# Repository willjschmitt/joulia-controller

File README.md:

# joulia-controller

Controller for the electric brewing hardware.

## Quickstart
Install Raspbian on a fresh SD card, and boot your Raspberry Pi.

Enable SSH (optional), for installing remotely. Make sure the password for the
main account is changed to a secure password. Enable I2C and SPI.

Install Anaconda (Miniconda), using the default options (installing to
`/home/pi/miniconda`):
```
wget http://repo.continuum.io/miniconda/Miniconda3-latest-Linux-armv7l.sh
bash Miniconda3-latest-Linux-arm71.sh
```
Answer all questions posed.

Clone the source:
```git clone https://github.com/willjschmitt/joulia-controller.git```

Create a conda environment and install the dependencies:
```
cd joulia-controller
/home/pi/miniconda3/bin/conda create --name joulia-controller python=3
source /home/pi/miniconda3/bin/activate joulia-controller
pip install -r requirements.txt
```

Create a log directory for joulia and change the owner to pi:
```
sudo mkdir /var/log/joulia
sudo chown pi:pi /var/log/joulia
```

### Automatic Startup
To automatically, launch the software on startup, install the contents from
`crontab` into the root cron table using:
```
sudo crontab -e
```

In the crontab, you must update the environment variables in angle brackets per
the definitions:
 * `JOULIA_WEBSERVER_HOST` - The webserver this controller should stream data to
   (usually `joulia.io`)
 * `JOULIA_WEBSERVER_AUTHTOKEN` - The authtoken provided in your dashboard on
   joulia.io, used to authenticate the controller and identify controller
   information.

### Manual Startup
Run the controller:
```
cd joulia-controller
source /home/pi/miniconda3/bin/activate joulia-controller
export JOULIA_WEBSERVER_HOST=joulia.io
export JOULIA_WEBSERVER_AUTHTOKEN=<insert token>
python main.py
```

## Connections to Hardware
This project is meant to be run on a Raspberry Pi and makes use of the GPIO pins.

### Analog Measurement
Make sure I2C is appropriately turned on on the Raspberry Pi. Install the Arduino I2C Analog Reader software onto the Arduino, so it can communicate the temperature measurements to the Raspberry Pi.

### Digital Control
Connect the Solid State Relay input gate for the Boil Kettle to Pin 0 on the Raspberry Pi.
Connect the Solid State Relay input gate for the Main Pump to Pin 1 on the Raspberry Pi.

## Related Projects
This project is part of the series of projects for the Joulia Brewing System:
* [joulia-webserver](https://github.com/willjschmitt/joulia-webserver) - Remote webserver to log data and allow for livestreaming of data to other clients and receive commands from other clients.
* [joulia-controller](https://github.com/willjschmitt/joula-controller) - This project.
* joulia-fermentation - Planned project to control the fementation operations.

## Licensing
Copyright 2016 William Schmitt. All Rights Reserved.

The intention is to make this project open-sourced, but at this moment is maintained under personal copyright until a few things can be worked through.

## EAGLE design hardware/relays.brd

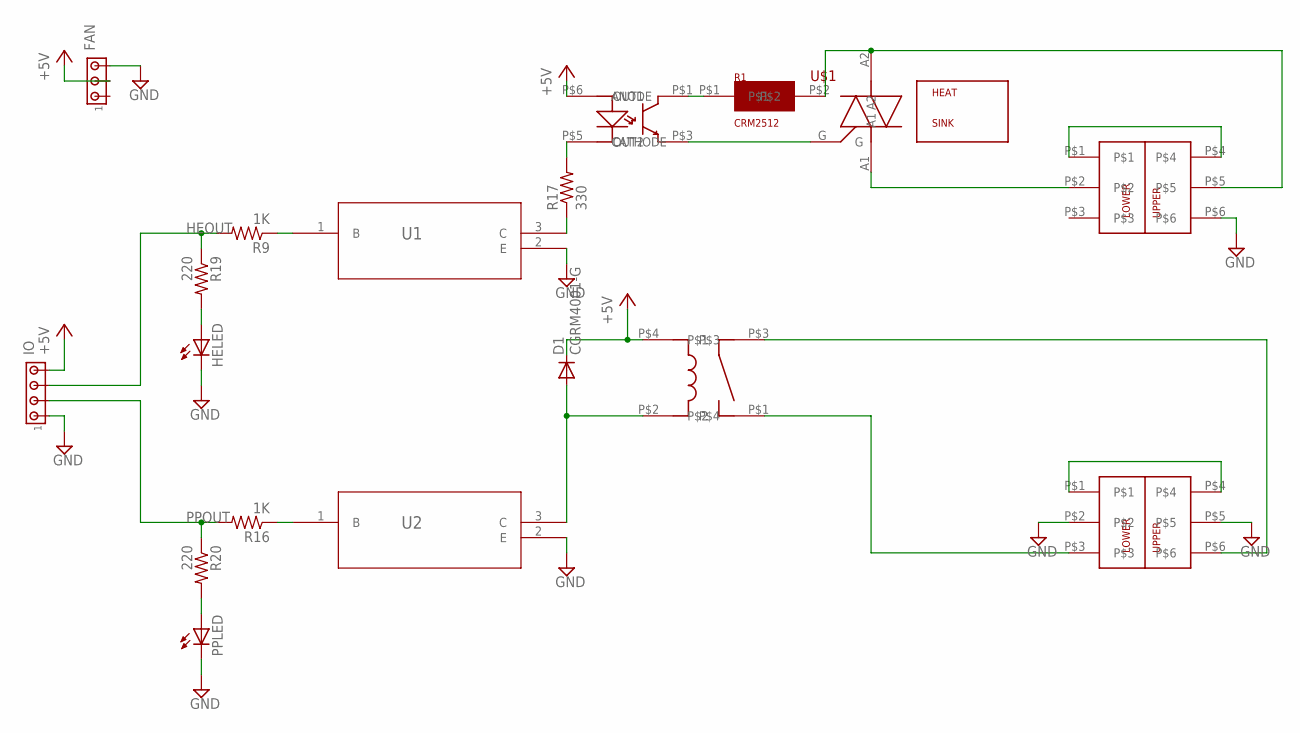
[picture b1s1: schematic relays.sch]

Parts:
D1: CGRM4001-G; SOD-123_MINI-SMA
FAN: MTA03-100; 10X03MTA
HELED: LED_ESML0603; LED_SML0603
IO: MTA04-100; 10X04MTA
PPLED: LED_ESML0603; LED_SML0603
R1: CRM2512; 2512(6432METRIC)
R9, R16: 1K; R0402
R17: 330; R1206
R19, R20: 220; R0402
U1, U2: MMBT2222ALT1G; SOT-23
U$1: T3050H-6I; TO-220
U$2: VM1-038-1AEHORIZONTAL; VM2-038-1AE
U$3: G5LE-1A4_DC5
U$4: PC1725041; PC-MKKDS1.5/3-5.08
U$5: MOC3020S; 6-SMD
U$6: PC1719028; PC-MKKDS5/3-9.5

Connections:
120H: U$3.P$1, U$4.P$3
120N: U$4.P$1, U$4.P$4
+5V: D1.C, FAN.2, IO.4, U$3.P$4, U$5.P$6 (ANODE)
+120: U$6.P$1, U$6.P$4
-120: U$1.A1, U$6.P$2
GND: FAN.3, HELED.C, IO.1, PPLED.C, U1.2 (E), U2.2 (E), U$4.P$2, U$4.P$5, U$6.P$6
HEOUT: IO.3, R9.2, R19.1
unnamed: R17.1, U1.3 (C)
unnamed: R17.2, U$5.P$5 (CATHODE)
unnamed: R9.1, U1.1 (B)
unnamed: R16.1, U2.1 (B)
unnamed: D1.A, U2.3 (C), U$3.P$2
unnamed: U$1.G, U$5.P$3 (OUT2)
unnamed: R1.P$1, U$5.P$1 (OUT1)
unnamed: R1.P$2, U$1.A2, U$6.P$5
unnamed: U$3.P$3, U$4.P$6
unnamed: HELED.A, R19.2
unnamed: PPLED.A, R20.2
PPOUT: IO.2, R16.2, R20.1

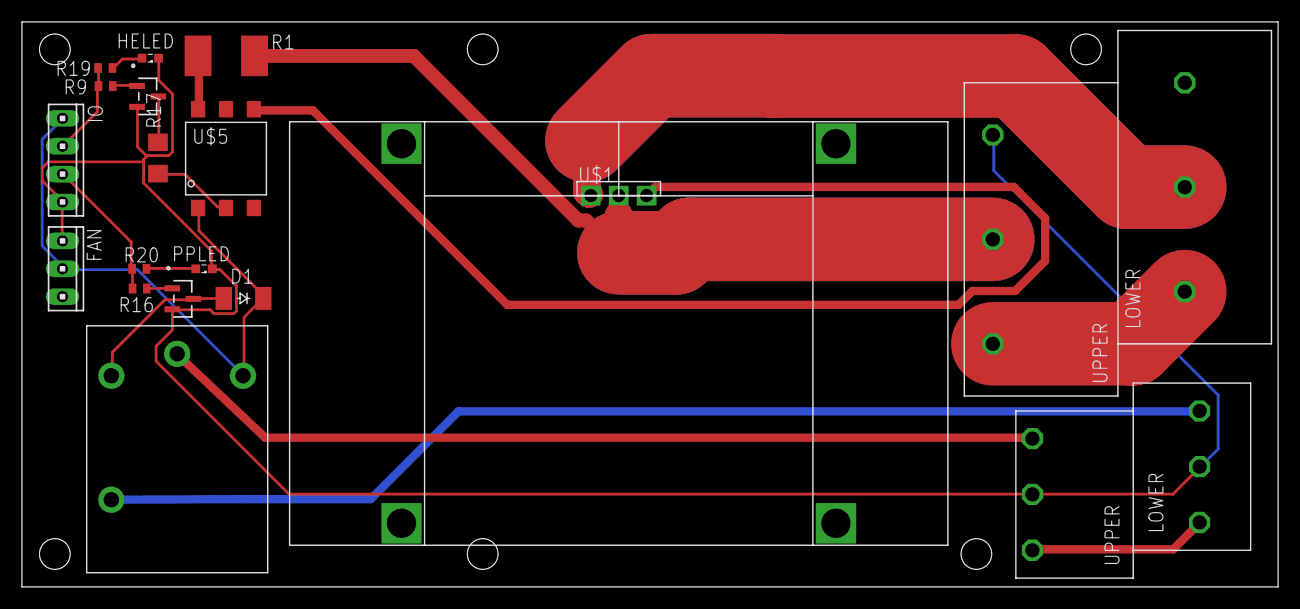
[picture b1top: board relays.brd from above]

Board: 2 copper layers, 114.5 x 51.5 mm, 19 parts (0 on the bottom side), 19 nets.

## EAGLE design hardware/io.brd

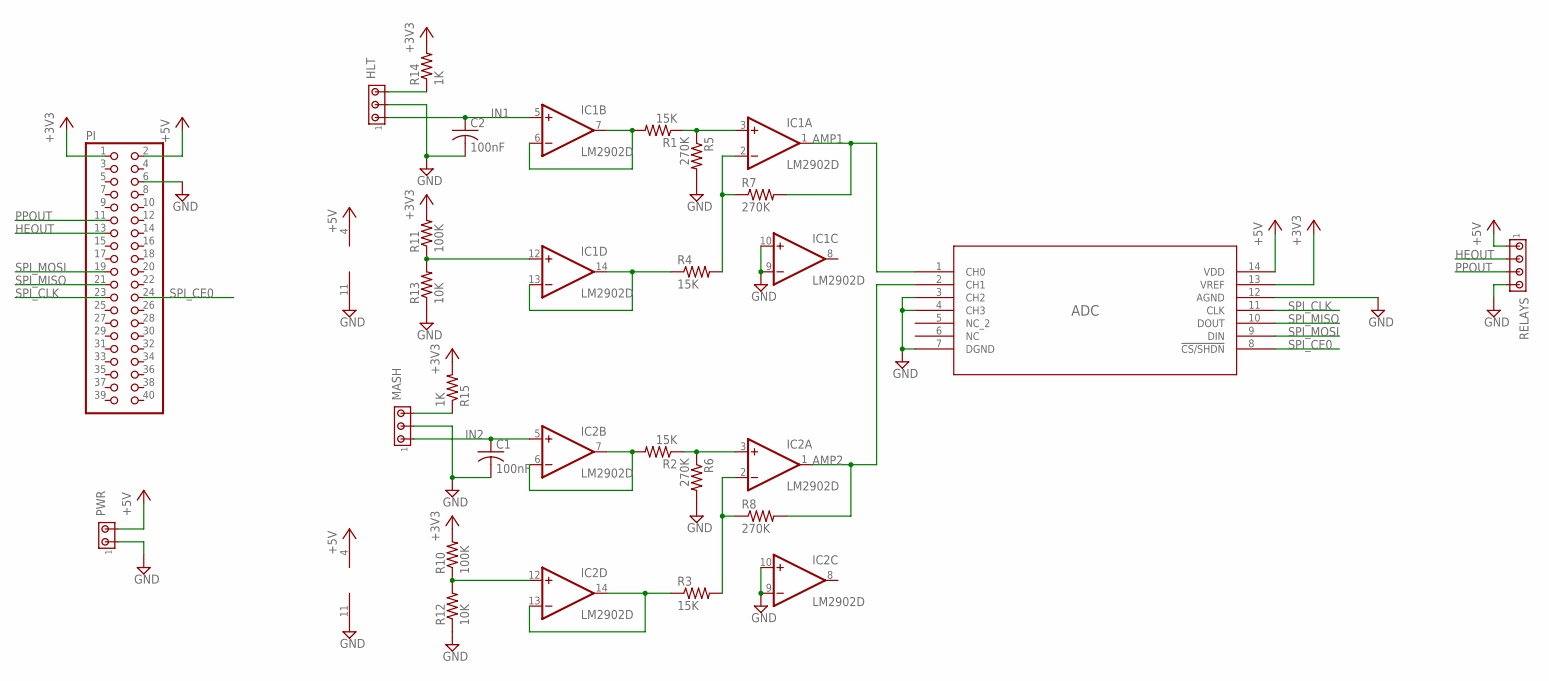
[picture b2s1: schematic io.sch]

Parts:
ADC: MCP3004-I/SL; SOIC14-N_MC
C1, C2: 100nF; C0402
HLT: MTA03-100; 10X03MTA
IC1, IC2: LM2902D; SO14
MASH: MTA03-100; 10X03MTA
PI: PINHD-2X20; 2X20
PWR: MTA02-100; 10X02MTA
R1, R2, R3, R4: 15K; R0402
R5, R6, R7, R8: 270K; R0402
R10, R11: 100K; R0402
R12, R13: 10K; R0402
R14, R15: 1K; R0402
RELAYS: MTA04-100; 10X04MTA

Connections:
+3V3: ADC.13 (VREF), PI.1, R10.2, R11.2, R14.2, R15.2
+5V: ADC.14 (VDD), IC1.4 (V+), IC2.4 (V+), PI.2, PWR.2, RELAYS.1
AMP1: ADC.1 (CH0), IC1.1 (OUT), R7.2
AMP2: ADC.2 (CH1), IC2.1 (OUT), R8.2
GND: ADC.3 (CH2), ADC.4 (CH3), ADC.7 (DGND), ADC.12 (AGND), C1.2, C2.2, HLT.2, IC1.9 (-IN), IC1.10 (+IN), IC1.11 (V-), IC2.9 (-IN), IC2.10 (+IN), IC2.11 (V-), MASH.2, PI.6, R5.2, R6.2, R12.1, R13.1, RELAYS.4
HEOUT: PI.13, RELAYS.2
IN1: C2.1, HLT.1, IC1.5 (+IN)
IN2: C1.1, IC2.5 (+IN), MASH.1
unnamed: IC1.6 (-IN), IC1.7 (OUT), R1.2
unnamed: IC1.3 (+IN), R1.1, R5.1
unnamed: IC1.12 (+IN), R11.1, R13.2
unnamed: IC1.2 (-IN), R4.2, R7.1
unnamed: IC1.13 (-IN), IC1.14 (OUT), R4.1
unnamed: IC2.6 (-IN), IC2.7 (OUT), R2.2
unnamed: IC2.3 (+IN), R2.1, R6.1
unnamed: IC2.2 (-IN), R3.2, R8.1
unnamed: IC2.12 (+IN), R10.1, R12.2
unnamed: IC2.13 (-IN), IC2.14 (OUT), R3.1
unnamed: MASH.3, R15.1
unnamed: HLT.3, R14.1
PPOUT: PI.11, RELAYS.3
SPI_CE0: ADC.8 (!CS/SHDN), PI.24
SPI_CLK: ADC.11 (CLK), PI.23
SPI_MISO: ADC.10 (DOUT), PI.21
SPI_MOSI: ADC.9 (DIN), PI.19

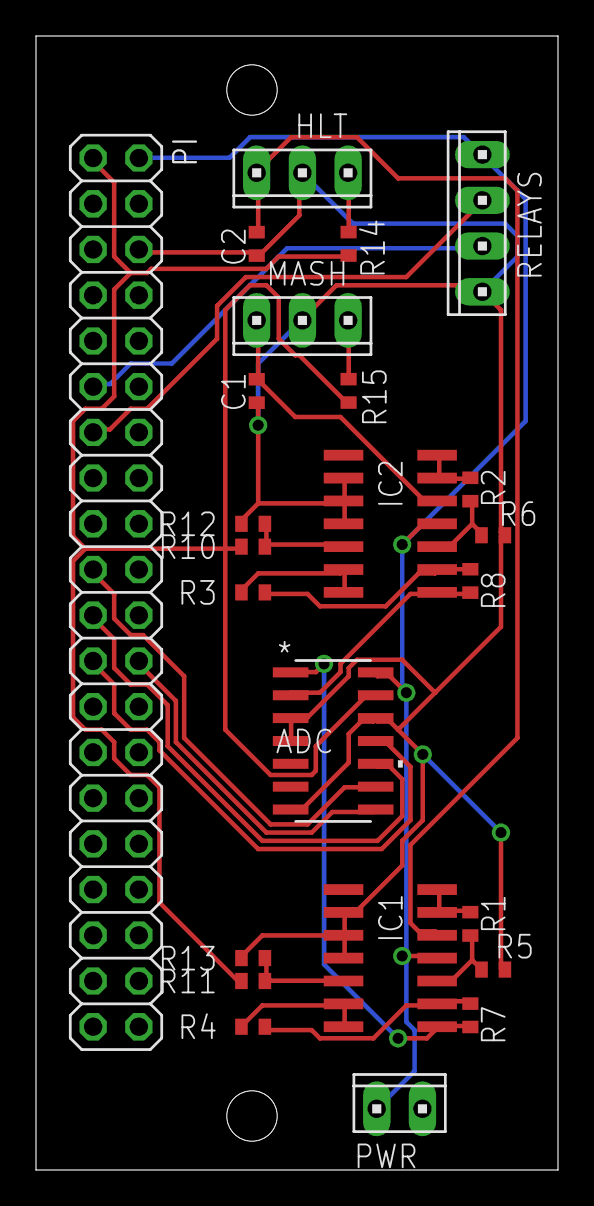
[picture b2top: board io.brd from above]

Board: 2 copper layers, 29.0 x 63.0 mm, 24 parts (0 on the bottom side), 25 nets.

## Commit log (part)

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2016-06-14 Adding permissions check.
2016-06-15 Better srtingification of boolean values in streaming.
2016-06-16 Permission granting is more smooth now. Race condition elimiated.
2016-06-18 Removing eclipse files.
2016-06-19 Switched subscribable and overridable variables to be descriptors, which makes their use much cleaner and simpler.
2016-06-19 Fixed the utility variable subscription.
2016-06-19 Fixed support for setting overrides.
2016-06-19 Added streamable variable implemented as a descriptor. Implemented timer to start.
    Need to keep datastreamer for the @property style variables.
2016-06-19 Cleaning up debug messages.
2016-06-19 Now overridable variables have streaming built in.
2016-06-22 Moved sensor grab into the try to call.
2016-06-22 Adding better logging and making true/false convert to 1/0.
2016-07-03 Brewery waits for the server to say it should be active and stops running controls when the server says it is no longer active.
2016-07-03 Controller now retreives recipe instance and initializes roughly based on it.
2016-07-03 Add temperature setpoints for items when offline that equal the current temps.
2016-08-03 Update README.md
    Adding copyright notice.
2016-08-23 Using env vars to pull some information now and using token auth for the server communication.
2016-08-23 Removing old c code, which originated from arduino code.
2016-09-13 Cleaning up pump module.
2016-09-17 Style improvements after runing a good deal of pylint.
2016-09-17 Added decorators to check if an instance is registered or subscribed already.
    Many style fixes.
2016-09-17 Style and bugfixes.
2016-09-17 Fixed several bugs from the refactoring in the variable layout.
2016-09-18 Adding gpio support
2016-09-18 Adding privileged info to readme
2016-09-18 Make sure we setup pinmode for GPIO, which crust doesn't do?
2016-10-05 Brewhouse id is now env var specified.
2016-10-12 Refactoring into parent class WebsocketVariable. Checking if websocket is connected before sending.
2016-10-14 Adding documentation for websocket handler.
2016-10-14 RTD sensor communicates via i2c.
2016-10-14 Changing i2c bus.
2016-10-14 Adding i2c installs to docker file.
2016-10-15 Fixed API call to smbus.
2016-10-23 Set websocket at open callback.
2017-02-08 Ignore pycharm files
2017-02-08 Adding register to vessel
2017-02-08 Refactoring variable code into new module
2017-02-14 Added tests for ManagedVariable and an additional decorator checking for subscribed or registered statuses.
    Add hook to inject a mocked requests service to mock request/response with a server not there.
2017-03-06 Lots of testing added. Split webserver communication code out into clients.
2017-03-07 Adding main board design.
    Adds a board connecting Raspberry Pi to ADC chip and amplifer circuits for RTD sensors. Transistor buffers for SSRs. Convenient plugs for power, SSRs, and RTDs.
2017-03-10 Fixed tests and 100% coverage on ManagedVariable
2017-03-10 Coverage for StreamingVariable.
2017-03-11 Full coverage in variables.py.
2017-03-11 Added test runner for ease in running coverage reports.
2017-03-11 Settings from env vars default to None.
2017-03-14 100% test coverage on joulia_webserver_client again.
2017-03-14 Cleanup brewhouse.
2017-03-14 Test coverage for utils.
2017-03-14 Added op_amp module for helping with op_amp circuits.
2017-03-14 Added helpers for calculating circuits.
2017-03-17 Coverage for first_order_lag.
2017-03-18 Supporting Python3.5 instead of 2.7. Refactored dsp a little.
2017-03-18 Abstracting DSP base class.
2017-03-18 Clock is now an injected dependency rather than an overridden one.
2017-03-18 Coverage for Integrator.
2017-03-18 Complete coverage for dsp module.
2017-03-18 Coverage for state_machine
2017-03-18 Abstracting gpio and coverage for pumps.
2017-03-18 Spelling fix.
2017-03-18 Tests for HeatedVessel.
2017-03-19 Coverage for vessels complete.
2017-03-19 Refactored temperature rate calculation into utils.
2017-03-19 Coverage for stub_gpio.
2017-03-19 More stub tests.
2017-03-19 Tests for stub_rtd_sensor.
2017-03-19 Full coverage for all the stubs.
2017-03-19 Removing unnecessary lines and adding pragma: no-cover comments for lines that are intentionally avoiding to be hit.
2017-03-19 Refactoring brewhouse.
2017-03-19 State machine passes in parent instance to states. States initialize with state machine.
2017-03-19 Brewhouse cleanup.
2017-03-19 Main cleanup.
2017-03-19 Stub increases identifier for larger tests.
2017-03-21 Fixing RtdSensor to use AnalogReader.
2017-03-21 Fixed webserver logging statement.
2017-03-21 Adding tests for stub_arduino_test.
2017-03-21 State machine now has next and previous actions.
2017-03-21 Added setting of state by name of the state class.
2017-03-21 More testing for brewhouse.
2017-03-21 Adding excluded lines.
2017-03-21 Testing for mashout recirculation.
2017-03-21 More states tested.
2017-03-21 Tests for boil.
2017-03-21 Closer to full coverage.
2017-03-21 Best coverage to reasonably achieve.
2017-03-21 Line cleanup.
2017-03-21 Adding RuntimeError to error check for import hack.
2017-03-21 Adding build and coverage badges.
2017-03-21 Fixing build badge.
2017-03-21 Another fix to reflect controller instead of webserver.
2017-04-30 Adding e-stop to HeatExchangedVessel.
2017-05-07 Controller downloads mash profile from server rather than using hardcoded one.
2017-05-21 Adding MCP3004 for use as an Analog Reader and refactorint into simple analog reader interface.
2017-05-22 Handling case to create MCP3008 when testing.
2017-05-22 Removing i2c arduino code, which has been moved to a new repo.
    This method is being deprecated for analog measurement anyways.
2017-05-29 Duty cycle for brewing vessel correctly turns on/off heating element.
    Refactored names for turn_off/on into disable/enable when their meaning was doubled.
2017-05-29 Fixing websocket address, which did not include ws endpoint.
2017-05-29 Adding trailing slash.
2017-05-29 Changing logging to format to string for optional envvars.
2017-05-30 Use settings for host.
2017-05-30 Add auth to start/stop client connections.
2017-06-04 Brewhouse id is retrieved programattically instead of being a setting.
2017-06-06 Fix recipe_instance from start watching.
2017-06-06 Websocket is correctly returned.
2017-06-07 Fix sensor name for subscribing variable identification.
2017-06-07 Brewery is started in watch_for_start.
2017-06-07 More logging for sending data.
2017-06-07 Adding Adafruit library as dep and logging if we need to fall back.
2017-06-09 Improving logging format and increasing default level to debug.
2017-06-09 Fixed RTD alpha values and RTD init order.
2017-06-09 Watches for start again after recipe termination.
2017-06-12 Fixing tests for start/stop.
2017-06-13 Adding FileNotFoundError as exception handling for Adafruit SPI library.
2017-06-19 Adds bidirectional managed variable, which StateMachine now uses.
    State.id not streamed with DataStreamer anymore.
2017-06-21 Correcting test failures for state machine/brewhouse.
2017-06-25 Increasing power trace width and adding input resistors to transistors.
2017-07-23 recipe-getting
    Adds client support for retrieving and setting the recipe.
    Refactors webclient libraries into separate package.
2017-07-23 Completes get_recipe test.
2017-07-23 Configuration-based brewhouse creation.
    Configuration is stored locally, but the idea is to make this extendable for more configurations, and soon be driven from the webserver.
2017-07-24 Add auto update manager.
    While the brewhouse is not brewing, checks for updates every 5 minutes and updates and restarts if there is an update available.
2017-07-24 Expanding coverage for client.
2017-07-25 Obtain recipe id instead of instance id.
2017-07-25 Fixed checkout of new commits.
2017-07-25 Changing update check to every 30 seconds.
2017-07-26 Create logging directory if it doesn't exist.
2017-07-26 Fallback to current directory for logging in Travis.
2017-07-26 Correcting TRAVIS detection.
2017-07-26 Fixing logging configuration.
2017-07-26 Assigning formatter to loggers
2017-07-26 Turn off update timer on reconnect.
    Ensures new timers are not spawned.
2017-07-26 Start/stop of update time out of start watcher.
2017-07-27 gitignore supports Eagle
    Got gitignore from https://github.com/github/gitignore/blob/master/Eagle.gitignore
2017-07-28 Adding crontab for auto start on reboot.
2017-07-28 Add exception logging for main.
2017-07-29 Adding alternate intended future launch method.
2017-07-29 Add Python 3.4 to Travis since RPi runs it.
2017-07-29 Removing Python3.5+ dependency on HTTPStatus.
2017-08-03 Instructions updated for fresh install.
    Also fixes path in crontab, using the default miniconda3 path.
2017-08-06 Retrieves configuration from webserver.
2017-08-08 Adding connectors and SSR to board
2017-08-08 Routing and rearrangement for power
2017-08-08 Routing of smaller traces.
2017-08-23 Adding first enclosure checkin
2017-09-06 Improves board layout and autorouting
2017-09-09 Updating heat sink outline.
2017-09-09 Complete wiring with HV circuit and rearrangement
2017-09-09 Adjust plugs to be consistently spaced.
2017-09-09 Rewiring pump to be consistent with HE.
2017-09-10 First pass of enclosure.
2017-09-25 Settings supply https vs http and wss vs ws
2017-09-25 Correcting naming for amplifier resistors.
2017-10-17 Thicker walls
2017-10-24 Removing gcode files.
2017-10-24 Correcting RTD holes.
    Also adjusts fan holes. Changes text to be recessed rather than appended.
2017-10-28 Adding LEDs and Fan Connector
2017-11-05 Correct HOST setting case in README
2017-11-08 Fixes test
2017-11-12 Adds release_update to deployment in travis.
2017-11-13 Wait for 10 seconds to allow networking to start up before
2017-11-19 Posts current states for controller to webserver
2017-11-19 Cleaning up extra text
2017-11-19 Adds cooling prep step.
2017-11-19 Identify API supports variable_type
2017-11-19 Handles overrides correctly.
2017-11-25 Refactors mash profile to fix bug
2017-11-26 Adds pylint to build
2017-11-26 Fixes pylint errors in dsp package
2017-11-26 Fixes pylint errors for measurement package.
2017-11-26 Fixes pylint errors for testing package.
2017-11-26 Refactors system into system module.
2017-11-26 Refactors main code to support simulation
    No longer doing soft fallbacks onto stub code. Stub code must be started explicitly.
2017-11-26 Adds reversal for temperature to rtd sensor.
2017-11-26 Analog reader support for writing stub values
2017-11-30 pylint fixes
2017-12-16 Print pylint version because of erroneous errors.
2017-12-16 Explicitly set astroid to older version to fix erroneous lint errors.
2017-12-28 Adding execute permission on deploy_docker.sh
2017-12-28 Making working directory for docker simulated.
2017-12-28 Only deploy once.
2017-12-30 Correct simulated main file name
2018-01-13 Correcting test data.
2018-01-13 Adding abstract interface for updater.
2018-01-13 Adding logging to updates.
2018-01-14 Adding logging to variable identification.
2018-01-14 Add value to reception log.
2018-01-14 Adding sensor id to subscribing message.
2018-01-15 Adds reconnection and resubscription.
    Solves #1
2018-01-15 Fixes in default variable type
2018-01-16 Adding permission grant log.
2018-01-16 Adding logging for all state transitions.
2018-01-16 Simplifying state logging.
2018-01-16 Updates server with updated software version.
2018-01-16 Update server with software version number even without hash change.
2018-01-16 Adding update logging when no hash available.
2018-01-16 Don't serialize brewhouse in POST call.
2018-01-16 Corrects update to be PUT instead of POST.
2018-01-17 Using json instead of data for nested data.
2018-01-17 Adding request body to a new exception in http client.
2018-01-17 Initialize simulated system in simulation mode.
2018-01-17 Startups are correct now.
    Simulations were not starting the simulator. Includes refactoring for start/end watch.
2018-01-20 Adding simulation logging.
2018-01-20 Correct watching for end request.
2018-02-04 Ignore log directory.
2018-02-09 Request no history on resubscriptions.
2018-03-17 Set Tornado version rather than latest.
2018-03-21 Fix linting error.
2018-03-24 Switching to mechanical relay for pump and horizontal heatsink.
2018-03-25 Removing extraneous resistor for relay.
2018-03-25 Switches two plugs for one board terminal for 240V connections.
2018-03-25 Move ground to 120V connection.
2018-03-26 Split relay into new board.
2018-04-04 IO and Relay boards are distinct

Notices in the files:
hardware/io.brd:
COPYRIGHT, 2017
